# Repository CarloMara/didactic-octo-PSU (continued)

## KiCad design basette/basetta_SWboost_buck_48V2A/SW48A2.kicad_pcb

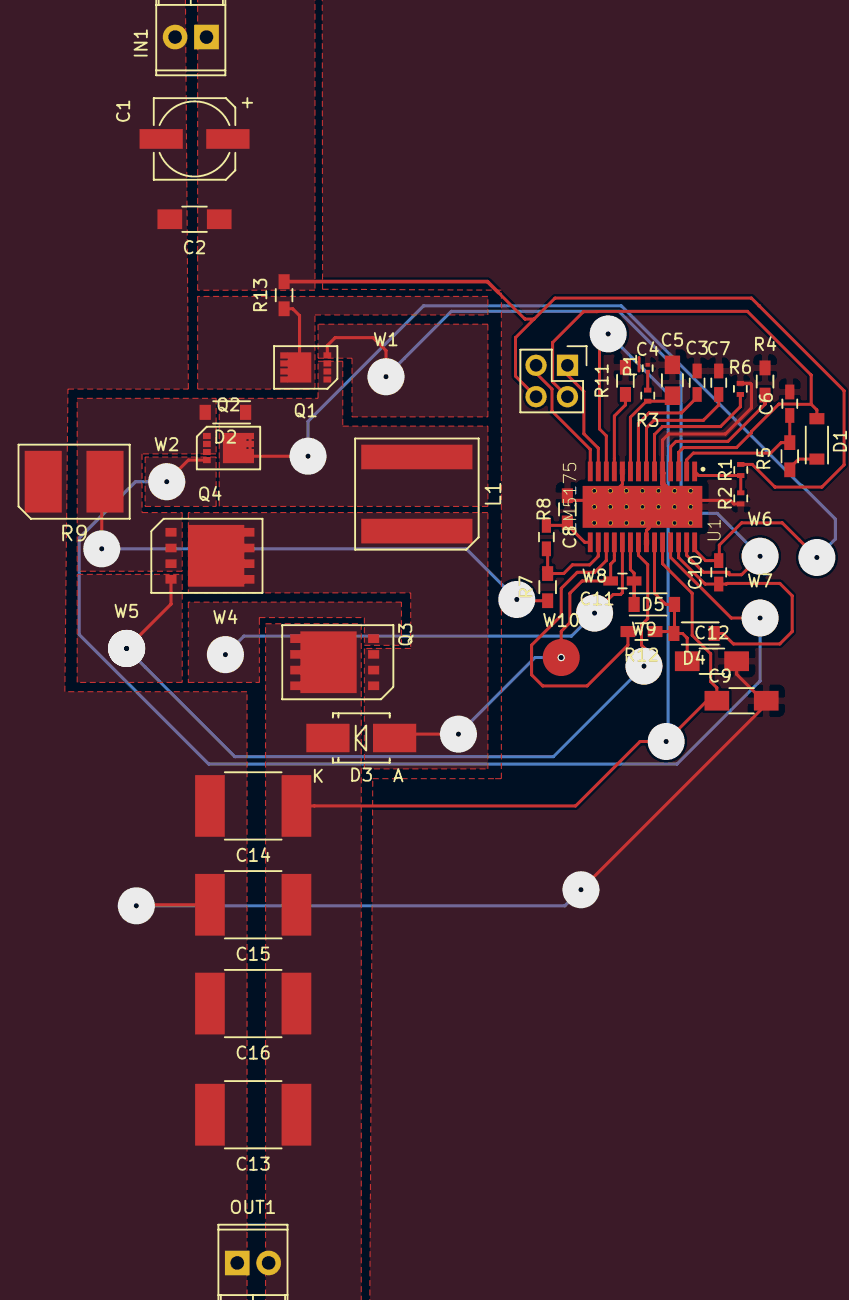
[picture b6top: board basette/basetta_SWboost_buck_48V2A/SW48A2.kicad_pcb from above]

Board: 2 copper layers, 51 parts (0 on the bottom side), 29 nets.

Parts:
C1: 68uF; c_elec_6.3x5.7
C2: 10uF; C_1206_HandSoldering
C3: 22nF; C_0603_HandSoldering
C4: 8.2nF; C_0201
C5: 27pF; C_0805_HandSoldering
C6: 220nF; C_0603_HandSoldering
C7: 270pF; C_0603_HandSoldering
C8: 47pF; C_0603_HandSoldering
C9, C12: 1uF; C_1206_HandSoldering
C10, C11: 100nF; C_0603_HandSoldering
C13, C14, C15: 4.7uF; C_2220_HandSoldering
C16: 15uF; C_2220_HandSoldering
D1, D2, D4, D5: SS24FL; SOD-123
D3: B260-13-F; SMB_Handsoldering
IN1: Screw_Terminal_1x02; TerminalBlock_Pheonix_MPT-2.54mm_2pol
L1: 8.2uH; SOIC-2
OUT1: Screw_Terminal_1x02; TerminalBlock_Pheonix_MPT-2.54mm_2pol
P1: CONN_02X02; Pin_Header_Straight_2x02
Q1, Q2: CSD16323Q3
Q3: CSD19534Q5A
Q4: CSD18531Q5A; CSD19534Q5A
R1: 249k; R_0402
R2: 32.4k; R_0402
R3: 41.2k; R_0402
R4: 93.1k; R_0603_HandSoldering
R5: 10; R_0603_HandSoldering
R6: 90.9k; R_0402
R7, R8: 100; R_0603_HandSoldering
R9: 9m; Shunt_Vishay
R11, R12: 20k; R_0603_HandSoldering
R13: poco; R_0603_HandSoldering
U1: LM5175; SOP65P640X120-28N
W1, W2, W4, W5, W6, W7, W8, W9, W10: TEST_1P; Measurement_Point_Round-SMD-Pad_Big

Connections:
/EN: R1.2, R2.1, U1.1
/HDRV1: Q1.2, U1.27, W1.1, W6.1
/HDRV2: Q3.2, U1.19, W4.1, W8.1
/ISNS+_1: C1.1, C2.1, IN1.1, P1.4, R1.1, R13.2
/ISNS-_1: D1.2, P1.2, Q1.1, R13.1, U1.3
/LDRV1: Q2.2, U1.25, W2.1, W7.1
/LDRV2: Q4.2, U1.21, W5.1, W9.1
/RCS_1: D2.2, Q2.3, Q4.3, R7.2, R9.1
/SW1: C10.2, D2.1, L1.1, Q1.3, Q2.1, U1.28
/SW2: C11.2, D3.2, L1.2, Q3.3, Q4.1, U1.18, W10.1
/VIN: C6.1, R5.2, U1.2
/VOUT: C9.1, C13.1, C14.1, C15.1, C16.1, D3.1, OUT1.2, Q3.1, U1.12, U1.24
Earth: C1.2, C2.2, C3.2, C4.2, C5.2, C6.2, C7.2, C9.2, C12.2, C13.2, C14.2, C15.2, C16.2, IN1.2, OUT1.1, R2.2, R4.2, R6.2, R8.2, R9.2, R11.2, U1.5, U1.10, U1.22, U1.29
unnamed: C3.1, U1.8
unnamed: C4.1, R3.2
unnamed: C5.1, R3.1, U1.9
unnamed: C7.1, U1.7
unnamed: C8.1, R8.1, U1.15
unnamed: C8.2, R7.1, U1.16
unnamed: C10.1, D4.1, U1.26
unnamed: C11.1, D5.1, U1.20
unnamed: C12.1, D4.2, D5.2, R12.1, U1.23
unnamed: D1.1, R5.1
unnamed: P1.1, U1.13
unnamed: P1.3, U1.14
unnamed: R4.1, U1.4
unnamed: R6.1, U1.6
unnamed: R11.1, U1.11
unnamed: R12.2, U1.17

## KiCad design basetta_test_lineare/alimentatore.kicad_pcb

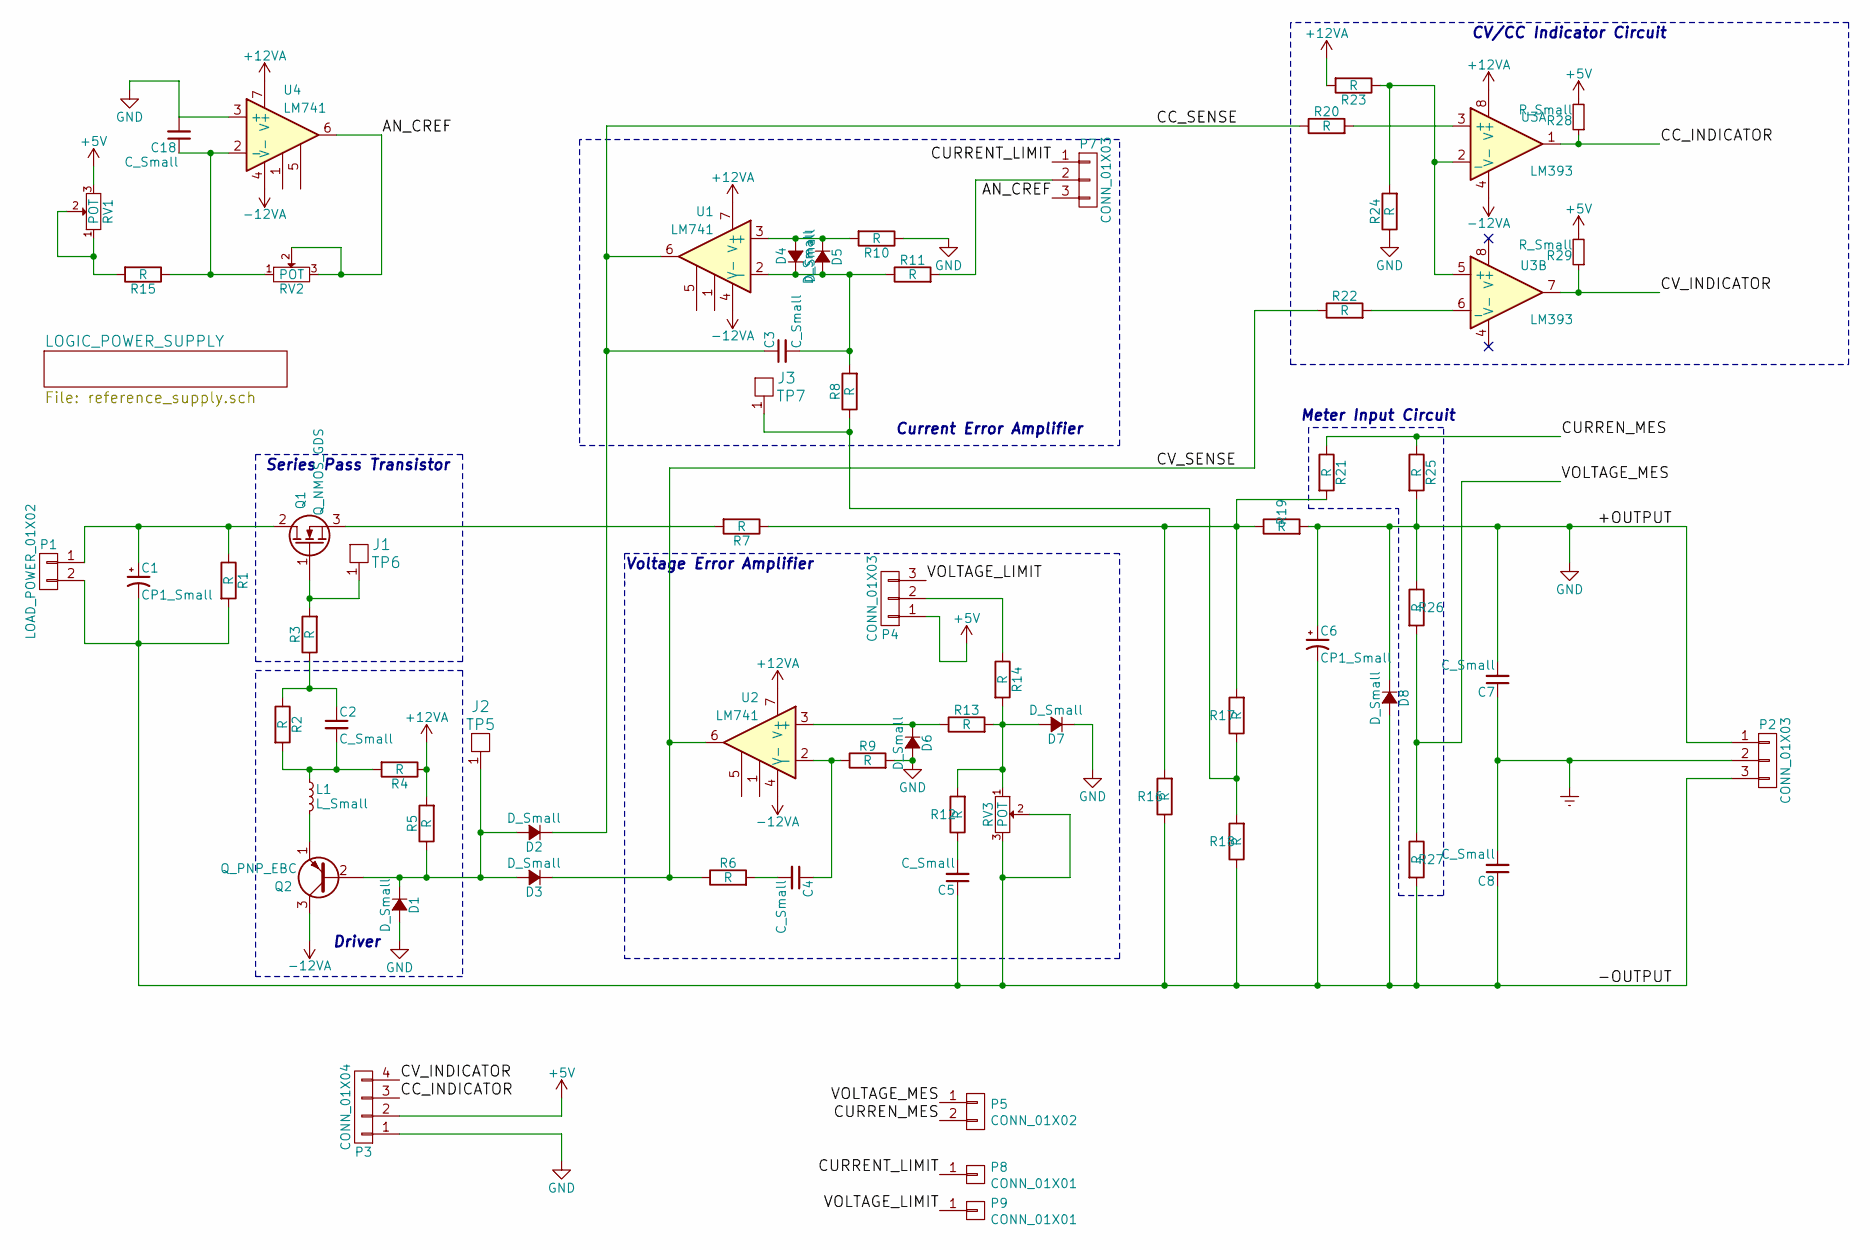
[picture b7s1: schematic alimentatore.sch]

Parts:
C1, C6: CP1_Small; C_Radial_D14_L31.5_P5
C2, C3, C4, C5, C18: C_Small; C_Disc_D3_P2.5
C7, C8: C_Small; C_Radial_D7.5_L11.2_P2.5
D1, D2, D3, D4, D5, D6, D7, D8: D_Small; Diode_DO-41_SOD81_Vertical_AnodeUp
J1: TP6; Pin_Header_Straight_1x01
J2: TP5; Pin_Header_Straight_1x01
J3: TP7; Pin_Header_Straight_1x01
L1: L_Small; Resistor_Horizontal_RM7mm
P1: LOAD_POWER_01X02; mors_2p
P2: CONN_01X03; mors_3p
P3: CONN_01X04; Pin_Header_Straight_1x04
P4, P7: CONN_01X03; Pin_Header_Straight_1x03
P5: CONN_01X02; Pin_Header_Straight_1x02
P8, P9: CONN_01X01; Pin_Header_Straight_1x01
Q1: Q_NMOS_GDS; TO-220_Neutral123_Vertical_LargePads
Q2: Q_PNP_EBC; TO-92_Rugged
R1, R2, R3, R4, R5, R6, R7, R8, R9, R10, R11, R12, R13, R14, R15, R16, R17, R18, R19, R20, R21, R22, R23, R24, R25, R26, R27: R; Resistor_Horizontal_RM10mm
R28, R29: R_Small; R_1210_HandSoldering
RV1, RV2, RV3: POT; Potentiometer_Trimmer-Piher-PT15-h5_vertical
U1, U2, U4: LM741; DIP-8_W7.62mm_LongPads
U3: LM393; DIP-8_W7.62mm_LongPads

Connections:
+5V: P3.2, P4.1, R28.2, R29.2, RV1.3; also elsewhere on the board
+12VA: R4.1, R5.2, R23.2, U1.7 (V+), U2.7 (V+), U3.8 (V+), U4.7 (V+); also elsewhere on the board
-12VA: Q2.3 (C), U1.4 (V-), U2.4 (V-), U3.4 (V-), U4.4 (V-); also elsewhere on the board
/-OUTPUT: C1.2, C5.1, C6.2, C8.1, D8.2 (A), P1.2, P2.3, R1.2, R16.1, R18.1, R27.2, RV3.2, RV3.3
/AN_CREF: P7.3, RV2.2, RV2.3, U4.6
/CC_INDICATOR: P3.3, R28.1, U3.1
/CC_SENSE: C3.1, D2.1 (K), R20.1, U1.6
/CURRENT_LIMIT: P7.1, P8.1
/CURREN_MES: P5.2, R21.1, R25.1
/CV_INDICATOR: P3.4, R29.1, U3.7
/CV_SENSE: D3.1 (K), R6.1, R22.1, U2.6
/VOLTAGE_LIMIT: P4.3, P9.1
/VOLTAGE_MES: P5.1, R26.2, R27.1
Earth: C7.1, C8.2, P2.2
GND: C6.1, C7.2, C18.2, D1.2 (A), D6.2 (A), D7.1 (K), D8.1 (K), P2.1, P3.1, R9.2, R10.1, R19.2, R24.1, R25.2, R26.1, U4.3 (+); also elsewhere on the board
unnamed: C1.1, P1.1, Q1.2 (D), R1.1
unnamed: C2.1, R2.1, R3.1
unnamed: C2.2, L1.1, R2.2, R4.2
unnamed: C3.2, D4.1 (K), D5.2 (A), R8.2, R11.1, U1.2 (-)
unnamed: C4.1, R9.1, U2.2 (-)
unnamed: C4.2, R6.2
unnamed: C5.2, R12.1
unnamed: C18.1, R15.1, RV2.1, U4.2 (-)
unnamed: D1.1 (K), D2.2 (A), D3.2 (A), J2.1, Q2.2 (B), R5.1
unnamed: D4.2 (A), D5.1 (K), R10.2, U1.3 (+)
unnamed: D6.1 (K), R13.1, U2.3 (+)
unnamed: D7.2 (A), R12.2, R13.2, R14.2, RV3.1
unnamed: J1.1, Q1.1 (G), R3.2
unnamed: J3.1, R8.1, R17.1, R18.2
unnamed: L1.2, Q2.1 (E)
unnamed: P4.2, R14.1
unnamed: P7.2, R11.2
unnamed: Q1.3 (S), R7.2
unnamed: R15.2, RV1.1, RV1.2
unnamed: R7.1, R16.2, R17.2, R19.1, R21.2
unnamed: R20.2, U3.3 (+)
unnamed: R22.2, U3.6 (_)
unnamed: R23.1, R24.2, U3.2 (_), U3.5 (+)

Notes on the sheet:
Voltage Error Amplifier
Current Error Amplifier
Driver
CV/CC Indicator Circuit
Series Pass Transistor
Meter Input Circuit

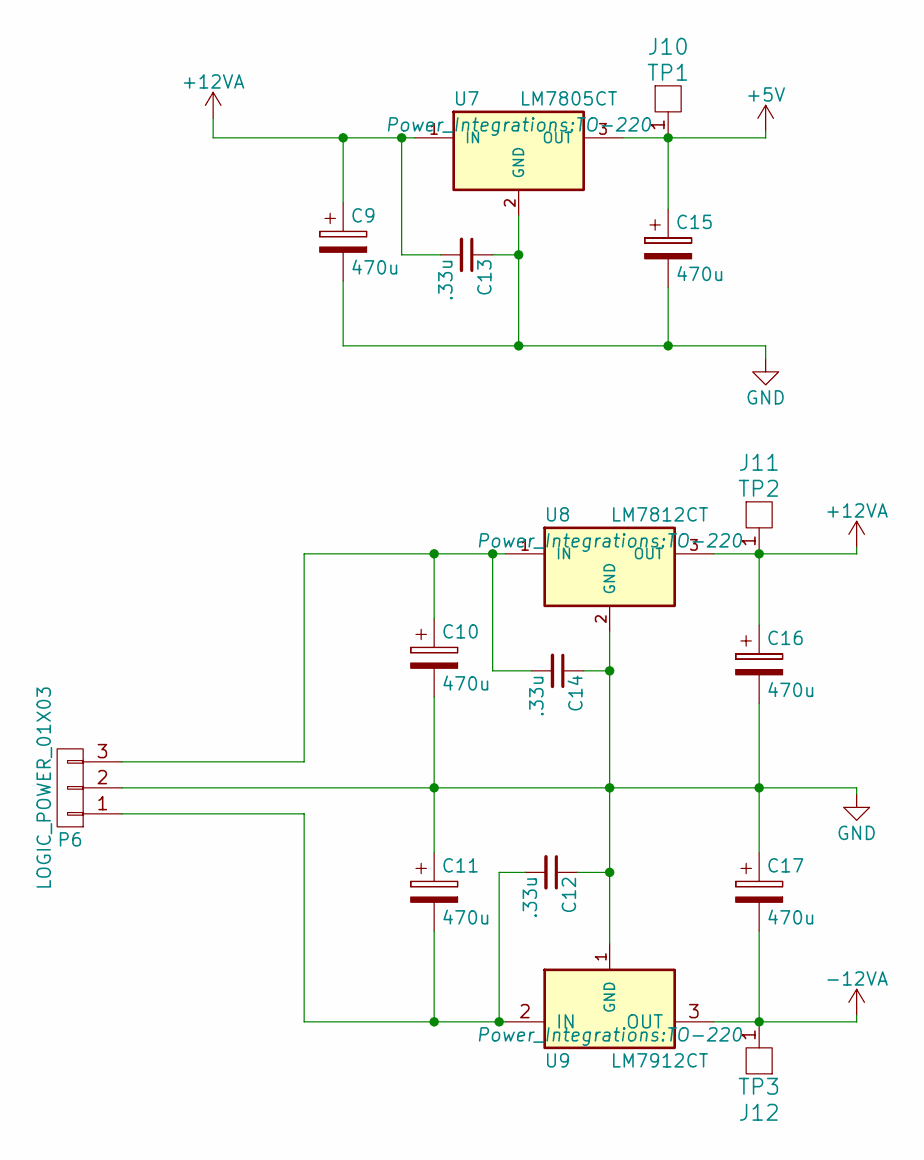
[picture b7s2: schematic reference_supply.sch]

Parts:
C9, C10, C11, C15, C16, C17: 470u; C_Radial_D8_L21_P3.8; Voltage 50V
C12, C13, C14: .33u; C_Disc_D3_P2.5; Voltage 50V
J10: TP1; Pin_Header_Straight_1x01
J11: TP2; Pin_Header_Straight_1x01
J12: TP3; Pin_Header_Straight_1x01
P6: LOGIC_POWER_01X03; mors_3p
U7: LM7805CT; TO-220
U8: LM7812CT; TO-220
U9: LM7912CT; TO-220

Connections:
+5V: C15.1, J10.1, U7.3 (OUT); also elsewhere on the board
+12VA: C9.1, C13.2, C16.1, J11.1, U7.1 (IN), U8.3 (OUT); also elsewhere on the board
-12VA: C17.2, J12.1, U9.3 (OUT); also elsewhere on the board
GND: C9.2, C10.2, C11.1, C12.1, C13.1, C14.1, C15.2, C16.2, C17.1, P6.2, U7.2 (GND), U8.2 (GND), U9.1 (GND); also elsewhere on the board
unnamed: C10.1, C14.2, P6.3, U8.1 (IN)
unnamed: C11.2, C12.2, P6.1, U9.2 (IN)

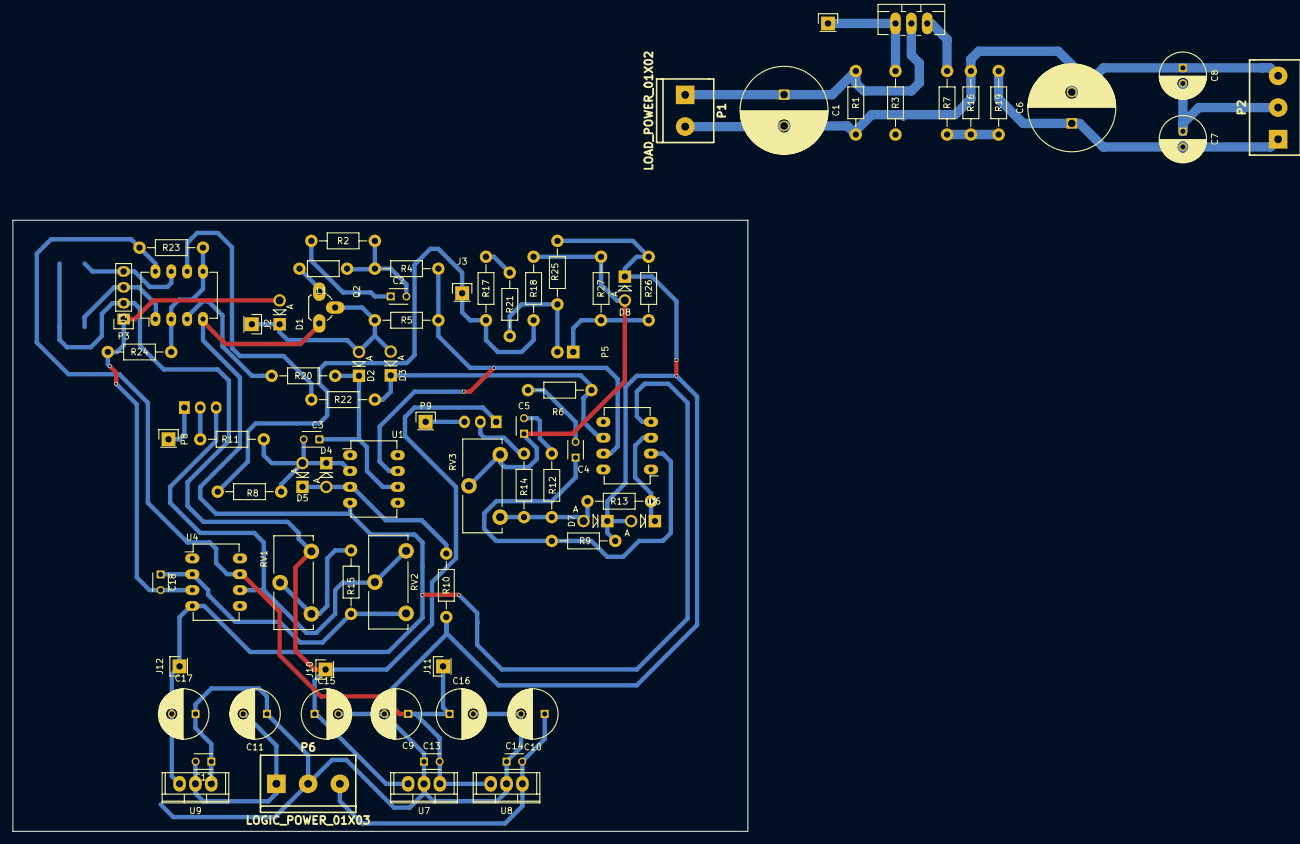
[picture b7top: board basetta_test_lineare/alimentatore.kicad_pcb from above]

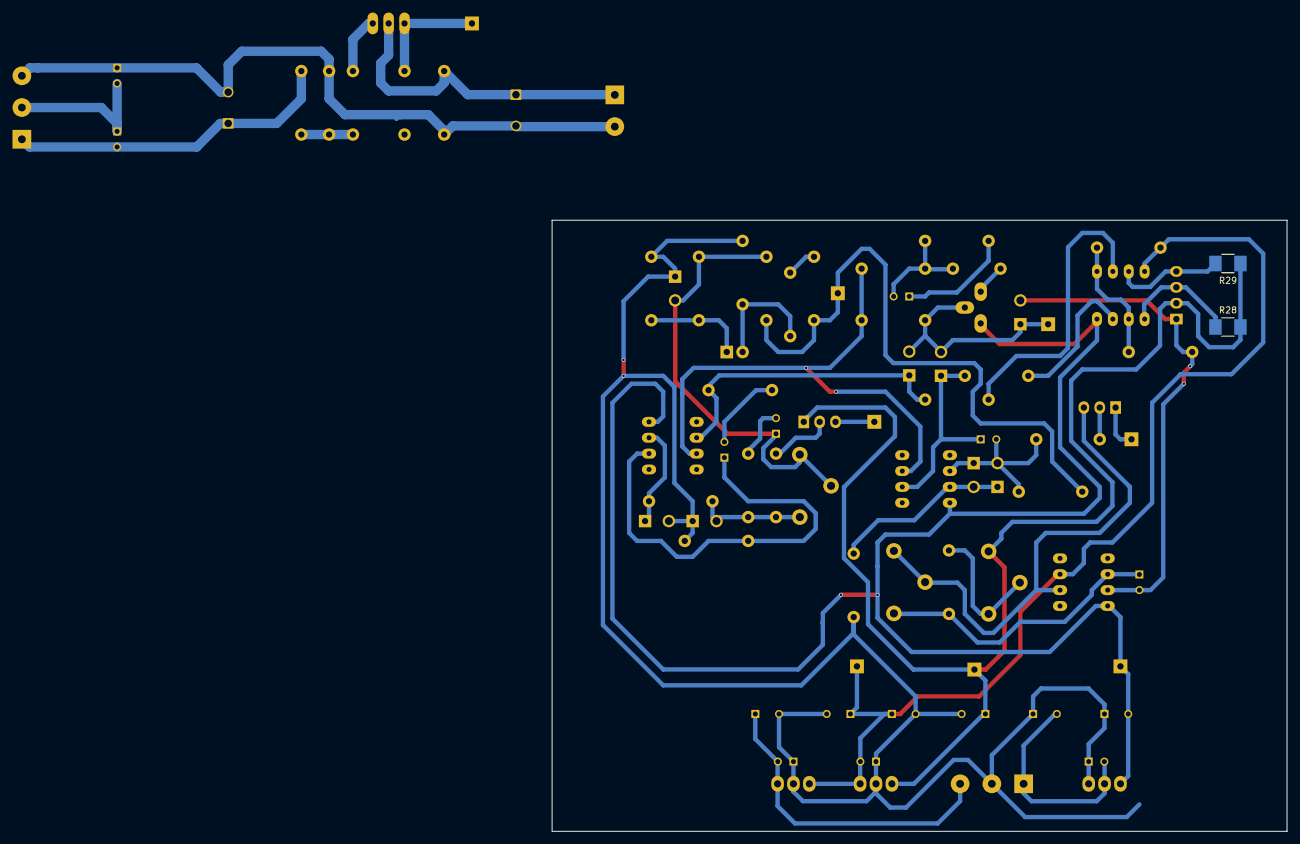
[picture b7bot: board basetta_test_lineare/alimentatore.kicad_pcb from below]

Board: 2 copper layers, 117.6 x 97.8 mm, 83 parts (2 on the bottom side), 40 nets.

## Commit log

2016-12-24 First Commit, first version of linear stage
2016-12-25 bleeding edge stuff
2016-12-25 README.md edited online with Bitbucket
2016-12-25 changing path to readme
2016-12-25 changing readme
2016-12-26 Updating schematics to reflect the dautherboard desing approch. The uC + DAC schematics has been removed. The dac reference has also been removed. in ordert to switch between pic or manual mode two j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
2016-12-31 Creata cartella con tutti i firmware. Creato esempio uart con mcc. trovato un bacco, ma aspetto che @gela lo riproduca su Windows.
2017-01-02 renamed lineare folder to reflect it's content
2017-01-02 removed lineare folder
2017-01-03 modification on uart example
2017-01-04 Updating PCB routing
2017-01-04 Created spreadsheet to understand in detail the DAC register
2017-01-06 Updating PCB routing and adding PCB edge
2017-01-06 Added a spreadsheet to explaint the varius DAC commands. The spreadsheet can also craft the command in the format used by the bus pirate. Created a project to test the MCC generated libraries. So far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
2017-01-06 Proceding with upgrading @Gela routing
2017-01-06 Same as before
2017-01-06 Splitted one of the daughterboard connector to allow a better routing
2017-01-07 Created the reference of the i2c implementation on mplab. This project it's now fully working, just swap the walues in the array.
2017-01-07 Created a test project that implements all of the PSU core function. Configured the MCC code with all of the peripherics (ADC, I2C, UART). Started to implement serial protocol. See future commit for 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
2017-01-09 Finished PCB "Parte lineare" routing
2017-01-09 added a firmware project for all of the functions modified pcb in order to make it with the matireals avaible
2017-01-12 Updated BOM list and components value
2017-01-27 changed some of the boarda. Added the file of the stm32 nucleo board.
2017-01-30 reorganized the simulation folder, added the switching tracking simulation
2017-02-01 Addin DC/DC boost-buck eeschema
2017-02-09 reorganized switching folder
2017-02-09 Added switching controller bom
2017-02-13 Adding schematic of boost/buck switching stage
2017-02-13 It say"commit"
2017-02-16 Finished footprints association -> ready for PCB routing!
2017-02-20 Added libraries, hopefully
2017-02-20 Ready for BOM
2017-02-20 Adding official TI PDF so @CarloMara is happy;
2017-02-23 Updated EESCHEMA , full footprin association and started PCB
2017-02-27 PCB update
2017-03-05 Reorganized Folder Structure
2017-03-05 Remove unnecessary files
2017-03-05 Progress on the routng of the H-Bridge
2017-03-06 Updated routing
2017-03-06 Moved resistor
2017-03-06 PCB of SW48A2
    Need more footprint for wire pad for single layer routing... need revision
2017-03-07 Updating PCB routing of sw48
2017-03-07 Finished PCB routing of SW48A2->ready for revision and prototyping
2017-03-09 More routing
2017-03-09 Routing and routing....
2017-03-13 Revised the linear part to adapt to the results of preliminary tests
2017-03-14 SW48A2 routing..
2017-03-23 Update of Sw48A2
2017-04-06 New board that include NUCLEO F303K8
2017-04-07 Adding lineare files
2017-04-07 work dir reorganized
2017-04-07 adedd kicad gitignore
2017-04-10 adedd front panel documents
    In the documents folder it's provided a pdf with the schematics of the bard with the display and the graphic display, and the encoder.
2017-04-11 New pcb about NUCLEO(ARM) and DAC for linear PSU regulation
2017-04-12 reviewed the schematics made by gela
    1-sistemare il bus
    2-finire la resistenza di biasing del reference
    3-mettere degli amplificatori per disaccopiare i dac
    4-predisporre per gli ingressi degli adc
    5-capire come gesire le alimentazioni ci penso io
2017-04-12 Adding annotation on kicad sheet
2017-04-17 Update..
2017-04-18 drawn a better schematic
    This new schemati reflects better the function of eatch passives and also uses less labes
2017-04-19 Labels on schematics, annotation and component assocation
    done
2017-04-19 Started Routing
    Changed pad assocation on the lm5175 footprint. Layed out the power components, in an efficient layout for shilding
2017-04-19 New netlist with lm5175 updated footprint
2017-04-19 Progress in routing
    Routed some of the passives
2017-04-20 Finished routing
2017-04-20 Deleting DAC and Reference
    Ciao Carlo!
2017-04-23 Shorted some wires for better performance
2017-04-24 Proceding with routing on Nucleo board
2017-04-24 Finish routing of basetta..
    Carlo must find something wrong...
2017-04-30 Progress on lineare rev3
    Created the kicad project and some of the libs!
2017-05-01 Progress on schematics
    DONE:
    -I2C insulation
    -DAC connection
    -DAC signal contitioning
    -Error amplifiers(both for voltage & current)
    -Pass element + gate control
2017-05-01 Removed useless libraries from project file
2017-05-01 Added linear regulators
2017-05-01 Picking footprints
2017-05-01 Revised work done by @NikoGela
    A few things have changed, to make it more clear schematic and routing changes are separated.
    #Schematic
    -removed the led that was used to show if the regulator was working
    -removed the power traces from the signal bus
    -broken out the connection for the I2C. see routing for futher details
    -changed the eletrolitic caps from THT to SMD
2017-05-03 Added mounting holes
2017-05-03 Relayed board to fit mounting holes
2017-05-04 Added docs
2017-05-04 Add special library for special components...
    Like dc dc converter,opamp etc..
2017-05-05 Created project for pd board
2017-05-05 Created footprint for dcdc converter
2017-05-05 New design for power distribution
2017-05-05 Flipped board to adjust for final board stack
2017-05-05 Final revision of schematic
    -added pullup resistor on i2c from digital side
    -added reference using lm4040. Our ic is the 2.5V version
    -checked the signal conditioning stage to get it working with changed reference
    WHEN TESTING IS POSSIBLE THAT THERE WILL BE SOME PROBLEMS WITH THE DAC & THE REFERENCE. The proposed solution is to cut the traces to the reference, use VDD as a reference and change the signal condi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
2017-05-05 Removed 75xx regulator from linear board
    In order to save space thoose components have been moved to the pd board
2017-05-05 Routed power delivery and linear reguletors
2017-05-05 Routed pd and regulators
2017-05-05 Added ground planes
2017-05-05 Created solid ground planes
    Cause thermal relief is for kids
2017-05-07 Added mountig holes and checked drc
2017-05-07 Added groundplanes and done DRC
2017-05-07 Added ground planes, moved I2C connector
    The I2C connector was moved to accomodate the changes done in the lineare board
2017-05-08 Swapped for LDO, ground planes
2017-05-08 Done things in power distribution
2017-05-08 Other major modification
2017-05-08 Adding hole for I2C bus in logic_power_distribution board
2017-05-08 Finished revising basetta_power_distribution
2017-05-08 Last change for power_distribution..
2017-05-08 Added labels
2017-05-08 NOW IT?S COMPLETE!
2017-05-22 Removed ground planes
    You can't see shit if they are off
